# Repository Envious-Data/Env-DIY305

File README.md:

# Env-DIY305
 A custom PCB implementation of the LTP305 as they are now discontinued.

## Info
the LTP305 is discontinued and I saw a project on hackaday where someone made their own LTP305 using 0201 LEDs on a DIP14 sized PCB so I thought since their pcb files were never released we can re-do it but open source it.

we've made our own but a couple of variations, hand soldering 0201 is hard and using PCBA is expensive for 0201 so there is a 0402 version, its not quite the same led position as the original displays but its functional and close enough as well as being decently cheap.

This is meant as a drop in replacement for the LTP305/TIL305 so we plan for it to work the same except without the diffuser cover and also with other colours.

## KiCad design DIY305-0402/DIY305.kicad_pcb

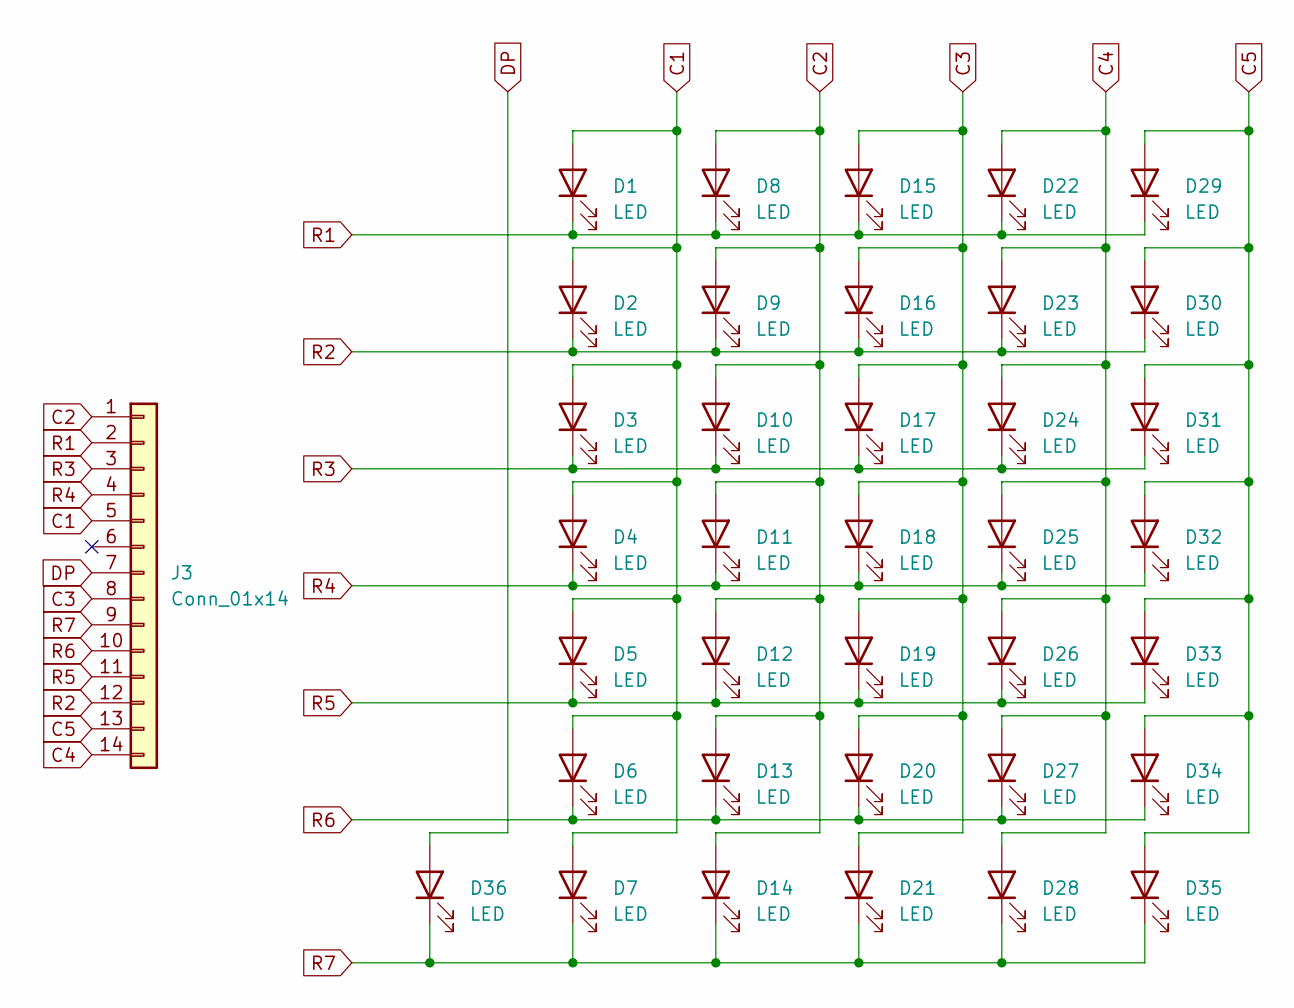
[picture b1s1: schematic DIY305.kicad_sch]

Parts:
D1, D2, D3, D4, D5, D6, D7, D8, D9, D10, D11, D12, D13, D14, D15, D16, D17, D18, D19, D20, D21, D22, D23, D24, D25, D26, D27, D28, D29, D30, D31, D32, D33, D34, D35, D36: LED; LED_0402_1005Metric
J3: Conn_01x14; PinHeader_1x14_P1.00mm_Vertical

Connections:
C1: D1.2 (A), D2.2 (A), D3.2 (A), D4.2 (A), D5.2 (A), D6.2 (A), D7.2 (A), J3.5
C2: D8.2 (A), D9.2 (A), D10.2 (A), D11.2 (A), D12.2 (A), D13.2 (A), D14.2 (A), J3.1
C3: D15.2 (A), D16.2 (A), D17.2 (A), D18.2 (A), D19.2 (A), D20.2 (A), D21.2 (A), J3.8
C4: D22.2 (A), D23.2 (A), D24.2 (A), D25.2 (A), D26.2 (A), D27.2 (A), D28.2 (A), J3.14
C5: D29.2 (A), D30.2 (A), D31.2 (A), D32.2 (A), D33.2 (A), D34.2 (A), D35.2 (A), J3.13
DP: D36.2 (A), J3.7
R1: D1.1 (K), D8.1 (K), D15.1 (K), D22.1 (K), D29.1 (K), J3.2
R2: D2.1 (K), D9.1 (K), D16.1 (K), D23.1 (K), D30.1 (K), J3.12
R3: D3.1 (K), D10.1 (K), D17.1 (K), D24.1 (K), D31.1 (K), J3.3
R4: D4.1 (K), D11.1 (K), D18.1 (K), D25.1 (K), D32.1 (K), J3.4
R5: D5.1 (K), D12.1 (K), D19.1 (K), D26.1 (K), D33.1 (K), J3.11
R6: D6.1 (K), D13.1 (K), D20.1 (K), D27.1 (K), D34.1 (K), J3.10
R7: D7.1 (K), D14.1 (K), D21.1 (K), D28.1 (K), D35.1 (K), D36.1 (K), J3.9

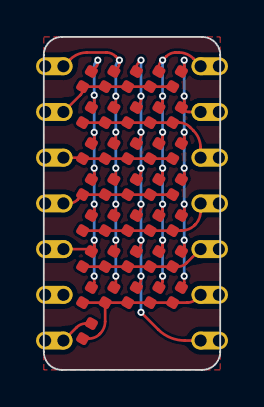
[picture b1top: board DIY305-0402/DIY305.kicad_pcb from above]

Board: 2 copper layers, 9.8 x 18.5 mm, 37 parts (0 on the bottom side), 13 nets.

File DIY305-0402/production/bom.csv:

Designator,Footprint,Quantity,Value,LCSC Part #
"D1, D10, D11, D12, D13, D14, D15, D16, D17, D18, D19, D2, D20, D21, D22, D23, D24, D25, D26, D27, D28, D29, D3, D30, D31, D32, D33, D34, D35, D36, D4, D5, D6, D7, D8, D9",0402,36,LED,
"J1, J2",PinHeader_1x07_P2.54mm_Vertical,2,Conn_01x07,

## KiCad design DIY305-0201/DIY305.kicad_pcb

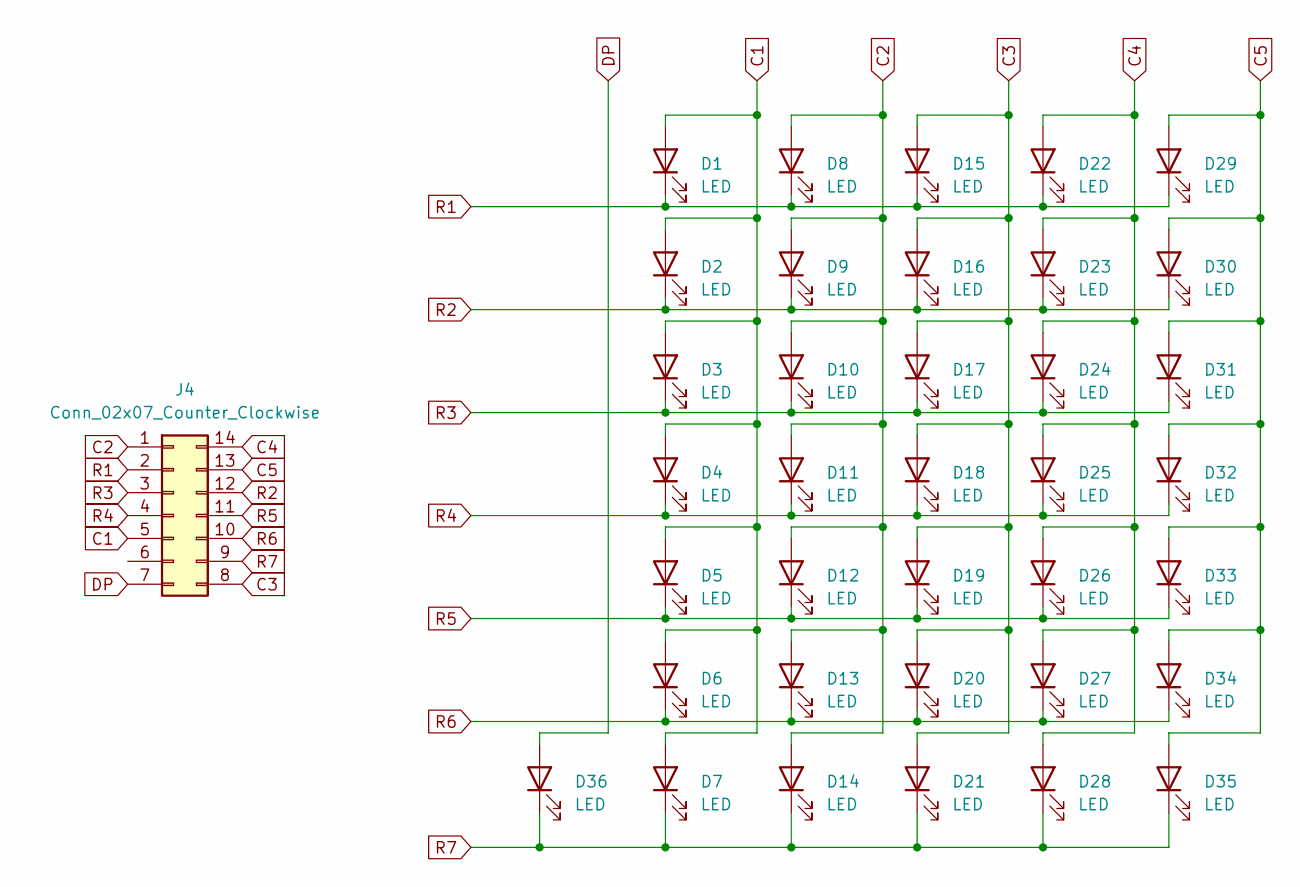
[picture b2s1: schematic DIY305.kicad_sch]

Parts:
D1, D2, D3, D4, D5, D6, D7, D8, D9, D10, D11, D12, D13, D14, D15, D16, D17, D18, D19, D20, D21, D22, D23, D24, D25, D26, D27, D28, D29, D30, D31, D32, D33, D34, D35, D36: LED; LED_0201_0603Metric
J4: Conn_02x07_Counter_Clockwise

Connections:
C1: D1.2 (A), D2.2 (A), D3.2 (A), D4.2 (A), D5.2 (A), D6.2 (A), D7.2 (A), J4.5
C2: D8.2 (A), D9.2 (A), D10.2 (A), D11.2 (A), D12.2 (A), D13.2 (A), D14.2 (A), J4.1
C3: D15.2 (A), D16.2 (A), D17.2 (A), D18.2 (A), D19.2 (A), D20.2 (A), D21.2 (A), J4.8
C4: D22.2 (A), D23.2 (A), D24.2 (A), D25.2 (A), D26.2 (A), D27.2 (A), D28.2 (A), J4.14
C5: D29.2 (A), D30.2 (A), D31.2 (A), D32.2 (A), D33.2 (A), D34.2 (A), D35.2 (A), J4.13
DP: D36.2 (A), J4.7
R1: D1.1 (K), D8.1 (K), D15.1 (K), D22.1 (K), D29.1 (K), J4.2
R2: D2.1 (K), D9.1 (K), D16.1 (K), D23.1 (K), D30.1 (K), J4.12
R3: D3.1 (K), D10.1 (K), D17.1 (K), D24.1 (K), D31.1 (K), J4.3
R4: D4.1 (K), D11.1 (K), D18.1 (K), D25.1 (K), D32.1 (K), J4.4
R5: D5.1 (K), D12.1 (K), D19.1 (K), D26.1 (K), D33.1 (K), J4.11
R6: D6.1 (K), D13.1 (K), D20.1 (K), D27.1 (K), D34.1 (K), J4.10
R7: D7.1 (K), D14.1 (K), D21.1 (K), D28.1 (K), D35.1 (K), D36.1 (K), J4.9

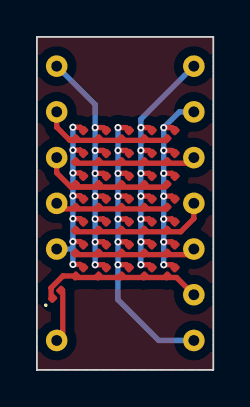
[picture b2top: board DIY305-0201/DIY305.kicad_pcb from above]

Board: 2 copper layers, 9.8 x 18.5 mm, 37 parts (0 on the bottom side), 13 nets.

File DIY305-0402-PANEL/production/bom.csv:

Designator,Footprint,Quantity,Value,LCSC Part #
"D1_10, D1_9, D1_8, D1_7, D1_6, D1_5, D1_4, D1_3, D1_2, D1, D10_10, D10_9, D10_8, D10_7, D10_6, D10_5, D10_4, D10_3, D10_2, D10, D11_10, D11_9, D11_8, D11_7, D11_6, D11_5, D11_4, D11_3, D11_2, D11, D12_10, D12_9, D12_8, D12_7, D12_6, D12_5, D12_4, D12_3, D12_2, D12, D13_10, D13_9, D13_8, D13_7, D13_6, D13_5, D13_4, D13_3, D13_2, D13, D14_10, D14_9, D14_8, D14_7, D14_6, D14_5, D14_4, D14_3, D14_2, D14, D15_10, D15_9, D15_8, D15_7, D15_6, D15_5, D15_4, D15_3, D15_2, D15, D16_10, D16_9, D16_8, D16_7, D16_6, D16_5, D16_4, D16_3, D16_2, D16, D17_10, D17_9, D17_8, D17_7, D17_6, D17_5, D17_4, D17_3, D17_2, D17, D18_10, D18_9, D18_8, D18_7, D18_6, D18_5, D18_4, D18_3, D18_2, D18, D19_10, D19_9, D19_8, D19_7, D19_6, D19_5, D19_4, D19_3, D19_2, D19, D2_10, D2_9, D2_8, D2_7, D2_6, D2_5, D2_4, D2_3, D2_2, D2, D20_10, D20_9, D20_8, D20_7, D20_6, D20_5, D20_4, D20_3, D20_2, D20, D21_10, D21_9, D21_8, D21_7, D21_6, D21_5, D21_4, D21_3, D21_2, D21, D22_10, D22_9, D22_8, D22_7, D22_6, D22_5, D22_4, D22_3, D22_2, D22, D23_10, D23_9, D23_8, D23_7, D23_6, D23_5, D23_4, D23_3, D23_2, D23, D24_10, D24_9, D24_8, D24_7, D24_6, D24_5, D24_4, D24_3, D24_2, D24, D25_10, D25_9, D25_8, D25_7, D25_6, D25_5, D25_4, D25_3, D25_2, D25, D26_10, D26_9, D26_8, D26_7, D26_6, D26_5, D26_4, D26_3, D26_2, D26, D27_10, D27_9, D27_8, D27_7, D27_6, D27_5, D27_4, D27_3, D27_2, D27",0402,200,LED,
"D28_10, D28_9, D28_8, D28_7, D28_6, D28_5, D28_4, D28_3, D28_2, D28, D29_10, D29_9, D29_8, D29_7, D29_6, D29_5, D29_4, D29_3, D29_2, D29, D3_10, D3_9, D3_8, D3_7, D3_6, D3_5, D3_4, D3_3, D3_2, D3, D30_10, D30_9, D30_8, D30_7, D30_6, D30_5, D30_4, D30_3, D30_2, D30, D31_10, D31_9, D31_8, D31_7, D31_6, D31_5, D31_4, D31_3, D31_2, D31, D32_10, D32_9, D32_8, D32_7, D32_6, D32_5, D32_4, D32_3, D32_2, D32, D33_10, D33_9, D33_8, D33_7, D33_6, D33_5, D33_4, D33_3, D33_2, D33, D34_10, D34_9, D34_8, D34_7, D34_6, D34_5, D34_4, D34_3, D34_2, D34, D35_10, D35_9, D35_8, D35_7, D35_6, D35_5, D35_4, D35_3, D35_2, D35, D36_10, D36_9, D36_8, D36_7, D36_6, D36_5, D36_4, D36_3, D36_2, D36, D4_10, D4_9, D4_8, D4_7, D4_6, D4_5, D4_4, D4_3, D4_2, D4, D5_10, D5_9, D5_8, D5_7, D5_6, D5_5, D5_4, D5_3, D5_2, D5, D6_10, D6_9, D6_8, D6_7, D6_6, D6_5, D6_4, D6_3, D6_2, D6, D7_10, D7_9, D7_8, D7_7, D7_6, D7_5, D7_4, D7_3, D7_2, D7, D8_10, D8_9, D8_8, D8_7, D8_6, D8_5, D8_4, D8_3, D8_2, D8, D9_10, D9_9, D9_8, D9_7, D9_6, D9_5, D9_4, D9_3, D9_2, D9",0402,160,LED,
"J3_10, J3_9, J3_8, J3_7, J3_6, J3_5, J3_4, J3_3, J3_2, J3",PinHeader_1x14_P1.00mm_Vertical,10,Conn_01x14,
"KiKit_MB_10_1, KiKit_MB_10_2, KiKit_MB_10_3, KiKit_MB_10_4, KiKit_MB_10_5, KiKit_MB_10_6, KiKit_MB_10_7, KiKit_MB_11_1, KiKit_MB_11_2, KiKit_MB_11_3, KiKit_MB_11_4, KiKit_MB_11_5, KiKit_MB_11_6, KiKit_MB_11_7, KiKit_MB_12_1, KiKit_MB_12_2, KiKit_MB_12_3, KiKit_MB_12_4, KiKit_MB_12_5, KiKit_MB_12_6, KiKit_MB_12_7, KiKit_MB_13_1, KiKit_MB_13_2, KiKit_MB_13_3, KiKit_MB_13_4, KiKit_MB_13_5, KiKit_MB_13_6, KiKit_MB_13_7, KiKit_MB_14_1, KiKit_MB_14_2, KiKit_MB_14_3, KiKit_MB_14_4, KiKit_MB_14_5, KiKit_MB_14_6, KiKit_MB_14_7, KiKit_MB_15_1, KiKit_MB_15_2, KiKit_MB_15_3, KiKit_MB_15_4, KiKit_MB_15_5, KiKit_MB_15_6, KiKit_MB_15_7, KiKit_MB_16_1, KiKit_MB_16_2, KiKit_MB_16_3, KiKit_MB_16_4, KiKit_MB_16_5, KiKit_MB_16_6, KiKit_MB_16_7, KiKit_MB_17_1, KiKit_MB_17_2, KiKit_MB_17_3, KiKit_MB_17_4, KiKit_MB_17_5, KiKit_MB_17_6, KiKit_MB_17_7, KiKit_MB_18_1, KiKit_MB_18_2, KiKit_MB_18_3, KiKit_MB_18_4, KiKit_MB_18_5, KiKit_MB_18_6, KiKit_MB_18_7, KiKit_MB_19_1, KiKit_MB_19_2, KiKit_MB_19_3, KiKit_MB_19_4, KiKit_MB_19_5, KiKit_MB_19_6, KiKit_MB_19_7, KiKit_MB_1_1, KiKit_MB_1_2, KiKit_MB_1_3, KiKit_MB_1_4, KiKit_MB_1_5, KiKit_MB_1_6, KiKit_MB_1_7, KiKit_MB_20_1, KiKit_MB_20_2, KiKit_MB_20_3, KiKit_MB_20_4, KiKit_MB_20_5, KiKit_MB_20_6, KiKit_MB_20_7, KiKit_MB_21_1, KiKit_MB_21_2, KiKit_MB_21_3, KiKit_MB_21_4, KiKit_MB_22_1, KiKit_MB_22_2, KiKit_MB_22_3, KiKit_MB_22_4, KiKit_MB_23_1, KiKit_MB_23_2, KiKit_MB_23_3, KiKit_MB_23_4, KiKit_MB_24_1, KiKit_MB_24_2, KiKit_MB_24_3, KiKit_MB_24_4, KiKit_MB_25_1, KiKit_MB_25_2, KiKit_MB_25_3, KiKit_MB_25_4, KiKit_MB_26_1, KiKit_MB_26_2, KiKit_MB_26_3, KiKit_MB_26_4, KiKit_MB_27_1, KiKit_MB_27_2, KiKit_MB_27_3, KiKit_MB_27_4, KiKit_MB_28_1, KiKit_MB_28_2, KiKit_MB_28_3, KiKit_MB_28_4, KiKit_MB_2_1, KiKit_MB_2_2, KiKit_MB_2_3, KiKit_MB_2_4, KiKit_MB_2_5, KiKit_MB_2_6, KiKit_MB_2_7, KiKit_MB_3_1, KiKit_MB_3_2, KiKit_MB_3_3, KiKit_MB_3_4, KiKit_MB_3_5, KiKit_MB_3_6, KiKit_MB_3_7, KiKit_MB_4_1, KiKit_MB_4_2, KiKit_MB_4_3, KiKit_MB_4_4, KiKit_MB_4_5, KiKit_MB_4_6, KiKit_MB_4_7, KiKit_MB_5_1, KiKit_MB_5_2, KiKit_MB_5_3, KiKit_MB_5_4, KiKit_MB_5_5, KiKit_MB_5_6, KiKit_MB_5_7, KiKit_MB_6_1, KiKit_MB_6_2, KiKit_MB_6_3, KiKit_MB_6_4, KiKit_MB_6_5, KiKit_MB_6_6, KiKit_MB_6_7, KiKit_MB_7_1, KiKit_MB_7_2, KiKit_MB_7_3, KiKit_MB_7_4, KiKit_MB_7_5, KiKit_MB_7_6, KiKit_MB_7_7, KiKit_MB_8_1, KiKit_MB_8_2, KiKit_MB_8_3, KiKit_MB_8_4, KiKit_MB_8_5, KiKit_MB_8_6, KiKit_MB_8_7, KiKit_MB_9_1, KiKit_MB_9_2, KiKit_MB_9_3, KiKit_MB_9_4, KiKit_MB_9_5, KiKit_MB_9_6, KiKit_MB_9_7",NPTH,172,NPTH,

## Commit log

2023-09-10 Version 1.0
2023-09-10 Created panelised version
2023-09-11 Version 2 with panelization and 0402 design
2023-09-11 Generated Panel
2023-09-12 created 305-0402 ALT and adjusted git ignore, might need another fix.
2023-09-12 finished up DIY-305-0402-ALT and fixed gitignore.
2023-09-12 panelized the board and generated gerber, single bom and cpl only.
2023-10-06 started work on manually paneling the pcb so I can get a more accurate price quote.
2024-01-15 Removal of old design
2024-01-15 Added largo panel
2024-02-15 Fixed silly flip error
2024-02-15 Added iPirie's logo and corrected single trace to reduce possibility of mechanical damage to PCB
2024-02-15 Added pannel
2024-03-01 Fixed spacing of pins and corrected orientation, made holes bigger and made tracks curvey with teardrops.
2024-04-01 generated step model for DIY305
2024-04-01 updated readme and license
2024-05-31 added castellations to the DIY305
2024-06-02 generated panel and production files
2024-06-02 made correct panel size
